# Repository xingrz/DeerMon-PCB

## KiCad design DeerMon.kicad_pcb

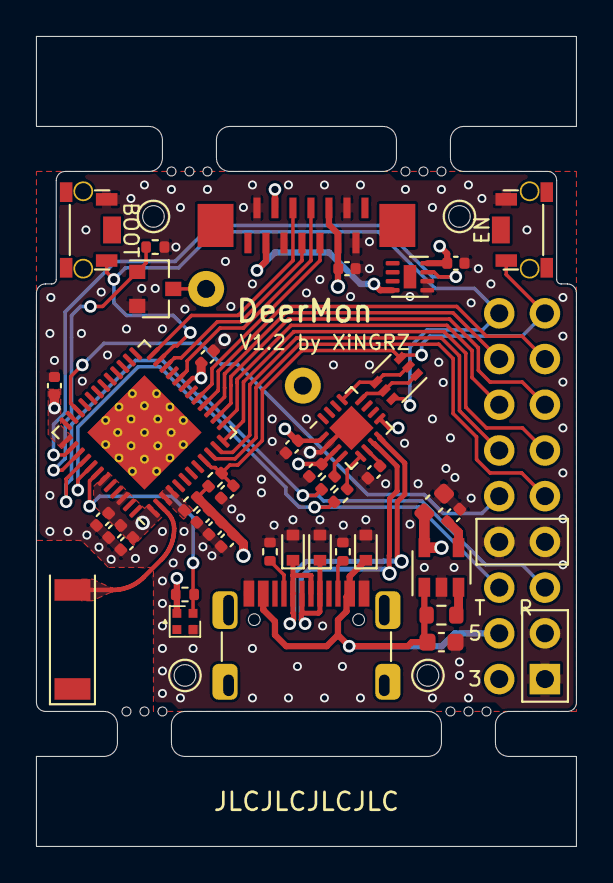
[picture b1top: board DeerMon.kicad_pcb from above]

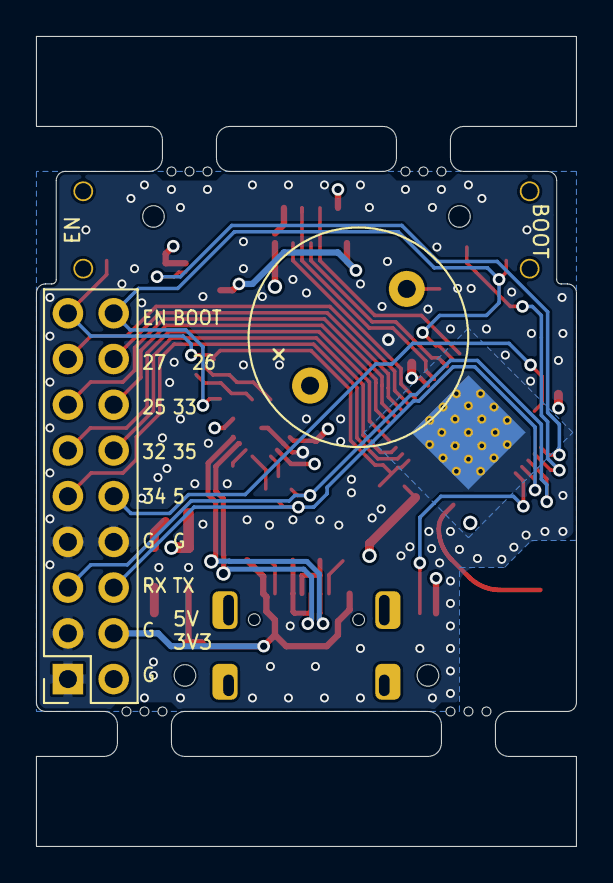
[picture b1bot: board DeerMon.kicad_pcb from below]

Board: 4 copper layers, 30.0 x 45.0 mm, 51 parts (2 on the bottom side), 37 nets.

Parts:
AE1: CA-C03; CrossAir_CA-C03
BZ1: HMB1206-05; HNDZ_TMB1206-05
C1, C2, C5, C12, C13, C16, C17: 0.1uF; C_0402_1005Metric
C3, C8, C11, C14, C15: 1uF; C_0402_1005Metric
C4: 10nF; C_0402_1005Metric
C6: 10uF; C_0402_1005Metric
C7: 100pF; C_0402_1005Metric
C9, C10: 10uF/25V; C_0603_1608Metric
CE1, CE2, CE3, CE4: CraftEdge; JLC_CRAFT_EDGE_3P
D1, D2, D3: LESD5Z5.0CT1G; D_SOD-523
D4: SK6805-EC15; OPSCO_SK68XX-EC15
H1, H2, H3, H4: Mount; MountingHole_1.2mm_M1
J1: TYPE-C-31-M-12; HRO_TYPE-C-31-M-12
J2: ZJY144S025; JS_AFC11-S14ICC-00
J3: GPIO; PinSocket_2x09_P2.54mm_Vertical
Q1: PUMH4; SOT-363_SC-70-6
Q2: 2N7002; SOT-23
R3, R4: 5.1K; R_0402_1005Metric
R7, R8: 1K; R_0402_1005Metric
R10: 0; R_0402_1005Metric
R11, R12, R13: 10K; R_0402_1005Metric
R14: 10K; R_0603_1608Metric
SW1: BOOT; SHOUHAN_TS24ZJ
SW2: EN; SHOUHAN_TS24ZJ
U1: CH343P; WQFN-16-1EP_3x3mm_P0.5mm_EP1.75x1.75mm
U2: BCT3220ELA-TR; DFN-8-1EP_2x2mm_P0.5mm_EP0.7x1.3mm
U3: SPX3819M5-L-3-3; SOT-23-5
U4: ESP32-PICO-V3-02; ESP32-PICO_QFN-48_7x7mm_P0.5mm_EP4.5x4.5mm_ThermalVias

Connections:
+3V3: C1.1, C3.1, C5.1, C6.1, C7.1, C8.1, C10.1, C12.1, C13.1, C14.1, C15.1, C16.1, D4.2, J2.4, J2.10, J2.11, J3.2, R10.1, R11.1, R12.1, U1.1, U2.8, U3.5, U4.1, U4.19, U4.37, U4.43, U4.46
+5V: BZ1.1, C2.1, C9.1, D3.1, J1.A4, J1.A9, J1.B4, J1.B9, J3.4, R14.2, U1.3, U1.9, U3.1
/BLK: U2.7, U4.38
/BOOT: J3.18, Q1.6, SW1.2, U4.23
/BZ_EN: Q2.1, R13.1, U4.39
/D+: D1.1, J1.A6, J1.B6, U1.7
/D-: D2.1, J1.A7, J1.B7, U1.8
/DTR: Q1.1, Q1.5, U1.12
/EN: C11.1, J3.17, Q1.3, R12.2, SW2.1, U4.9
/ESP_RX: J3.5, R8.1, U4.40
/ESP_TX: J3.6, R7.1, U4.41
/IO5: J3.10, U4.34
/IO25: J3.13, U4.14
/IO26: J3.16, U4.15
/IO27: J3.15, U4.16
/IO32: J3.11, U4.12
/IO33: J3.14, U4.13
/IO34: J3.9, U4.10
/IO35: J3.12, U4.11
/LCD_DC: J2.7, U4.22
/LCD_RST: J2.6, U4.24
/LCD_SCL: J2.9, U4.17
/LCD_SDA: J2.8, U4.20
/LEDK: J2.3, U2.4
/RGB: D4.1, R11.2, U4.42
/RTS: Q1.2, Q1.4, U1.13
/USB_RX: R7.2, U1.5
/USB_TX: R8.2, U1.4
GND: C1.2, C2.2, C3.2, C4.2, C5.2, C6.2, C7.2, C8.2, C9.2, C10.2, C11.2, C12.2, C13.2, C14.2, C15.2, C16.2, C17.2, D1.2, D2.2, D3.2, D4.4, J1.A1, J1.A12, J1.B1, J1.B12, J2.2, J2.5, J2.12, J2.13, J3.1, J3.3, J3.7, J3.8, Q2.2, R3.1, R4.1, R13.2, SW1.1, SW2.2, U1.2, U1.17, U2.5, U2.6, U3.2, U4.49
unnamed: AE1.1, U4.2
unnamed: BZ1.2, Q2.3
unnamed: C4.1, U3.4
unnamed: C17.1, U1.6
unnamed: J1.A5, R3.2
unnamed: J1.B5, R4.2
unnamed: R10.2, U4.3, U4.4
unnamed: R14.1, U3.3

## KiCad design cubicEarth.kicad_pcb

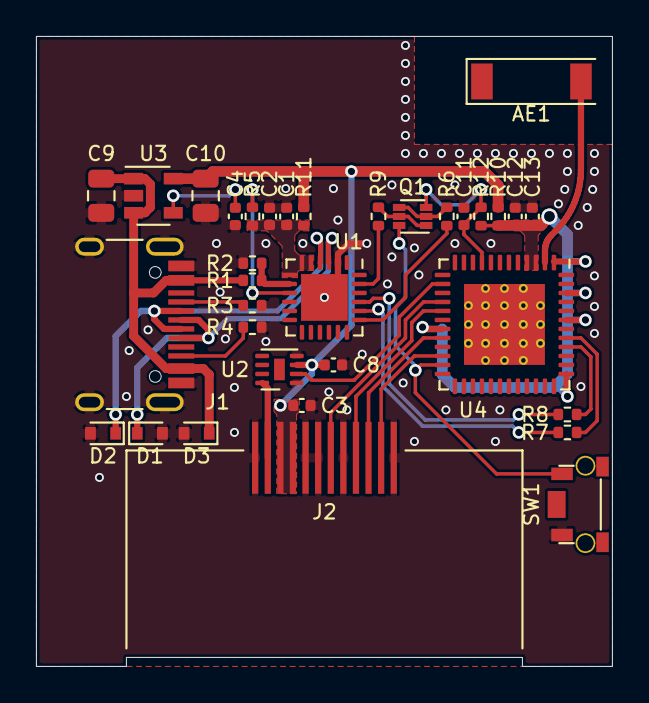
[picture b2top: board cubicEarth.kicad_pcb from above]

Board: 2 copper layers, 32.0 x 35.0 mm, 34 parts (0 on the bottom side), 29 nets.

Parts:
AE1: CA-C03; CrossAir_CA-C03
C1: 4.7uF; C_0402_1005Metric
C2, C13: 100nF; C_0402_1005Metric
C3, C8, C11: 1uF; C_0402_1005Metric
C4: 10nF; C_0402_1005Metric
C9, C10: 10uF/25V(10%); C_0805_2012Metric
C12: 10uF/6.3V; C_0402_1005Metric
D1, D2, D3: LESD5Z5.0CT1G; D_SOD-523
J1: TYPE-C-31-M-12; HRO_TYPE-C-31-M-12
J2: ZJY154T-PG04; ZJY_01x12_P0.7x4.0mm
Q1: BC847BVC-7; SOT-563
R1: 22.1K(1%); R_0402_1005Metric
R2: 47.5K(1%); R_0402_1005Metric
R3, R4: 5.1K; R_0402_1005Metric
R5, R7, R8: 1K; R_0402_1005Metric
R6, R9, R12: 10K; R_0402_1005Metric
R10, R11: 0; R_0402_1005Metric
SW1: TS24ZJ; SHOUHAN_TS24ZJ
U1: CP2102N-A02-GQFN24R; QFN-24-1EP_4x4mm_P0.5mm_EP2.6x2.6mm
U2: AW9364DNR; AW9364DNR_DFN2x2-8L
U3: LP2992AIM5X-3.3; SOT-23-5
U4: ESP32-PICO-V3-02; ESP32-PICO_QFN-48_7x7mm_P0.5mm_EP4.5x4.5mm_ThermalVias

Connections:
+3V3: C3.1, C8.1, C10.1, J2.3, J2.4, R10.2, R11.2, U2.3, U3.5
+5V: C9.1, D3.1, J1.A4, J1.A9, J1.B4, J1.B9, R1.2, U3.1, U3.3
/BLK: U2.2, U4.14
/BOOT: Q1.6, SW1.2, U4.23
/D+: D1.1, J1.A6, J1.B6, U1.3
/D-: D2.1, J1.A7, J1.B7, U1.4
/DTR: R9.1, U1.23
/EN: C11.1, Q1.3, R12.2, U4.9
/ESP_RX: R8.1, U4.40
/ESP_TX: R7.1, U4.41
/ESP_VDD: C12.1, C13.1, R10.1, R12.1, U4.1, U4.3, U4.4, U4.19, U4.37, U4.43, U4.46
/LCD_DC: J2.7, U4.16
/LCD_RES: J2.11, U4.22
/LCD_SCL: J2.9, U4.17
/LCD_SDA: J2.10, U4.20
/LEDK: J2.2, U2.8
/RTS: R6.2, U1.19
/USB_RX: R7.2, U1.20
/USB_TX: R8.2, U1.21
GND: C1.2, C2.2, C3.2, C4.2, C8.2, C9.2, C10.2, C11.2, C12.2, C13.2, D1.2, D2.2, D3.2, J1.A1, J1.A12, J1.B1, J1.B12, J1.S1, J2.1, J2.5, J2.6, J2.8, J2.12, R2.2, R3.1, R4.1, SW1.1, U1.2, U1.25, U2.1, U2.4, U3.2, U4.49
unnamed: AE1.1, U4.2
unnamed: C1.1, C2.1, R5.2, R11.1, U1.5, U1.6, U1.7
unnamed: C4.1, U3.4
unnamed: J1.A5, R3.2
unnamed: J1.B5, R4.2
unnamed: Q1.1, Q1.5, R9.2
unnamed: Q1.2, Q1.4, R6.1
unnamed: R1.1, R2.1, U1.8
unnamed: R5.1, U1.9

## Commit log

2021-06-22 Init repository
2021-06-22 Collect documents
2021-06-22 Done basic sch
2021-06-22 Adjust pinout for ESP32-PICO-V3-02
2021-06-22 Finish BOM
2021-06-24 [WIP] PCB layout
2021-06-24 Use an SOT-563 dual NPN instead of 2 separated NPN
2021-06-24 Use LP2992AIM5X-3.3 instead of AMS1117-3.3
2021-06-25 PCB layout almost done
2021-06-25 Looks better
2021-06-26 Looks even better
2021-06-30 Add outline rulers
2022-02-20 Rename to DeerMon
2022-02-20 Clean up
2022-02-20 Replace LP2992 with SPX3819
2022-02-20 Use 1.44" LCD, use PCB antenna
2022-02-22 Done schematic
2022-02-23 PCB layout
2022-02-23 Convert to 4 layers PCB
2022-02-24 Update PCB layout
2022-02-25 Redraw power
2022-02-28 Finish PCB
2022-02-28 Update BOM and documents
2022-02-28 Finish silk screen
2022-02-28 Output manufacturing documents
2022-03-03 Correct PCB thickness
2022-03-03 Add more documents
2022-03-03 Adjust outline for buttons
2022-03-03 Update gerber
2022-03-11 Add M1 mount points
2022-03-23 Add craft edges and JLCJLCJLCJLC
2022-03-24 Fix BOM
2022-03-24 Use mechanical drills instead of outline for mounting and positioning
2022-04-01 Use IO19/22 instead of reserved IO6/11 for BLK and BZ_EN
2022-04-01 Use DDC114TH instead of BC847BVC, with position of 10K resistor fixed
2022-04-04 Better tracks
2022-04-04 Update silks
2022-04-04 Update for RGB
2022-04-04 Drop position holes, let JLC add it
2022-04-04 Better vias
2022-04-06 Replace DDC114TH with PUMH4
2022-04-06 Add alternative backlight design driving by a MOSFET
2022-04-24 Replace AW9364 with BCT3220
2022-04-25 Use CH343P instead of CP2102N-A02-GQFN24R
2022-04-25 Better layout
2022-04-26 Adjust craft edges and silks
2022-04-30 Update documents
2022-05-03 Correct package for SK6805-EC15
